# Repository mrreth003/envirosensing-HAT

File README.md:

# Envirosensing HAT PCB Design Group Project (EEE3088F)

## Design Team

- Ethan Morris (MRRETH003)
- Ethan Meknassi (MKNETH002)
- Moutloatsi Setlogelo (STLMOU001)

## Project Overview

Our project involves designing a proximity sensor surveillance device using a HAT (Hardware Attached on Top) powered by either a microcontroller or a battery. The HAT utilizes a PIR motion sensor to detect the presence of a person or animal, triggering a buzzer to sound an alert. Detection logs are stored and can be accessed by the user.

## Hardware Requirements

To operate this device, you will need the following hardware:
- **Power Source**: Either an STM32000 microcontroller or an 18650 battery.
- **USB Cable**: Male USB A to Male Micro USB B Cable for data retrieval.
- **Computer**: For data retrieval and battery charging.

## Hardware Setup

### Microcontroller Power Setup
1. Place the microcontroller under the device using the inner set of connectors.
2. Connect the 5V pin of the microcontroller to pin "J3" on the device. Pin "J3" is the leftmost pin on the third row of connectors when the device is in its default position (buzzer at the top left).

### Battery Power Setup
1. Insert the 18650 battery into the battery holder.
2. Connect the USB to Micro USB cable to the device and your computer for data retrieval or battery charging. The battery should be placed in the position indicated by the red rectangle in the attached picture.

## Basic Operating Instructions

1. Power on the device using the battery.
2. Create movement close to the device (e.g., wave your hand 5-10 cm away from the device). The buzzer should beep, indicating the device is operational.
3. To retrieve the detection log, connect the device to a computer using the USB to Micro USB cable.

## License

The license information for this project can be found in the Git repository.

[Project Repository](https://gitlab.com/mrreth003/envirosensing-hat/-/tree/main/)

Kind Regards,

Ethan Morris, Ethan Meknassi, and Moutloatsi Setlogelo

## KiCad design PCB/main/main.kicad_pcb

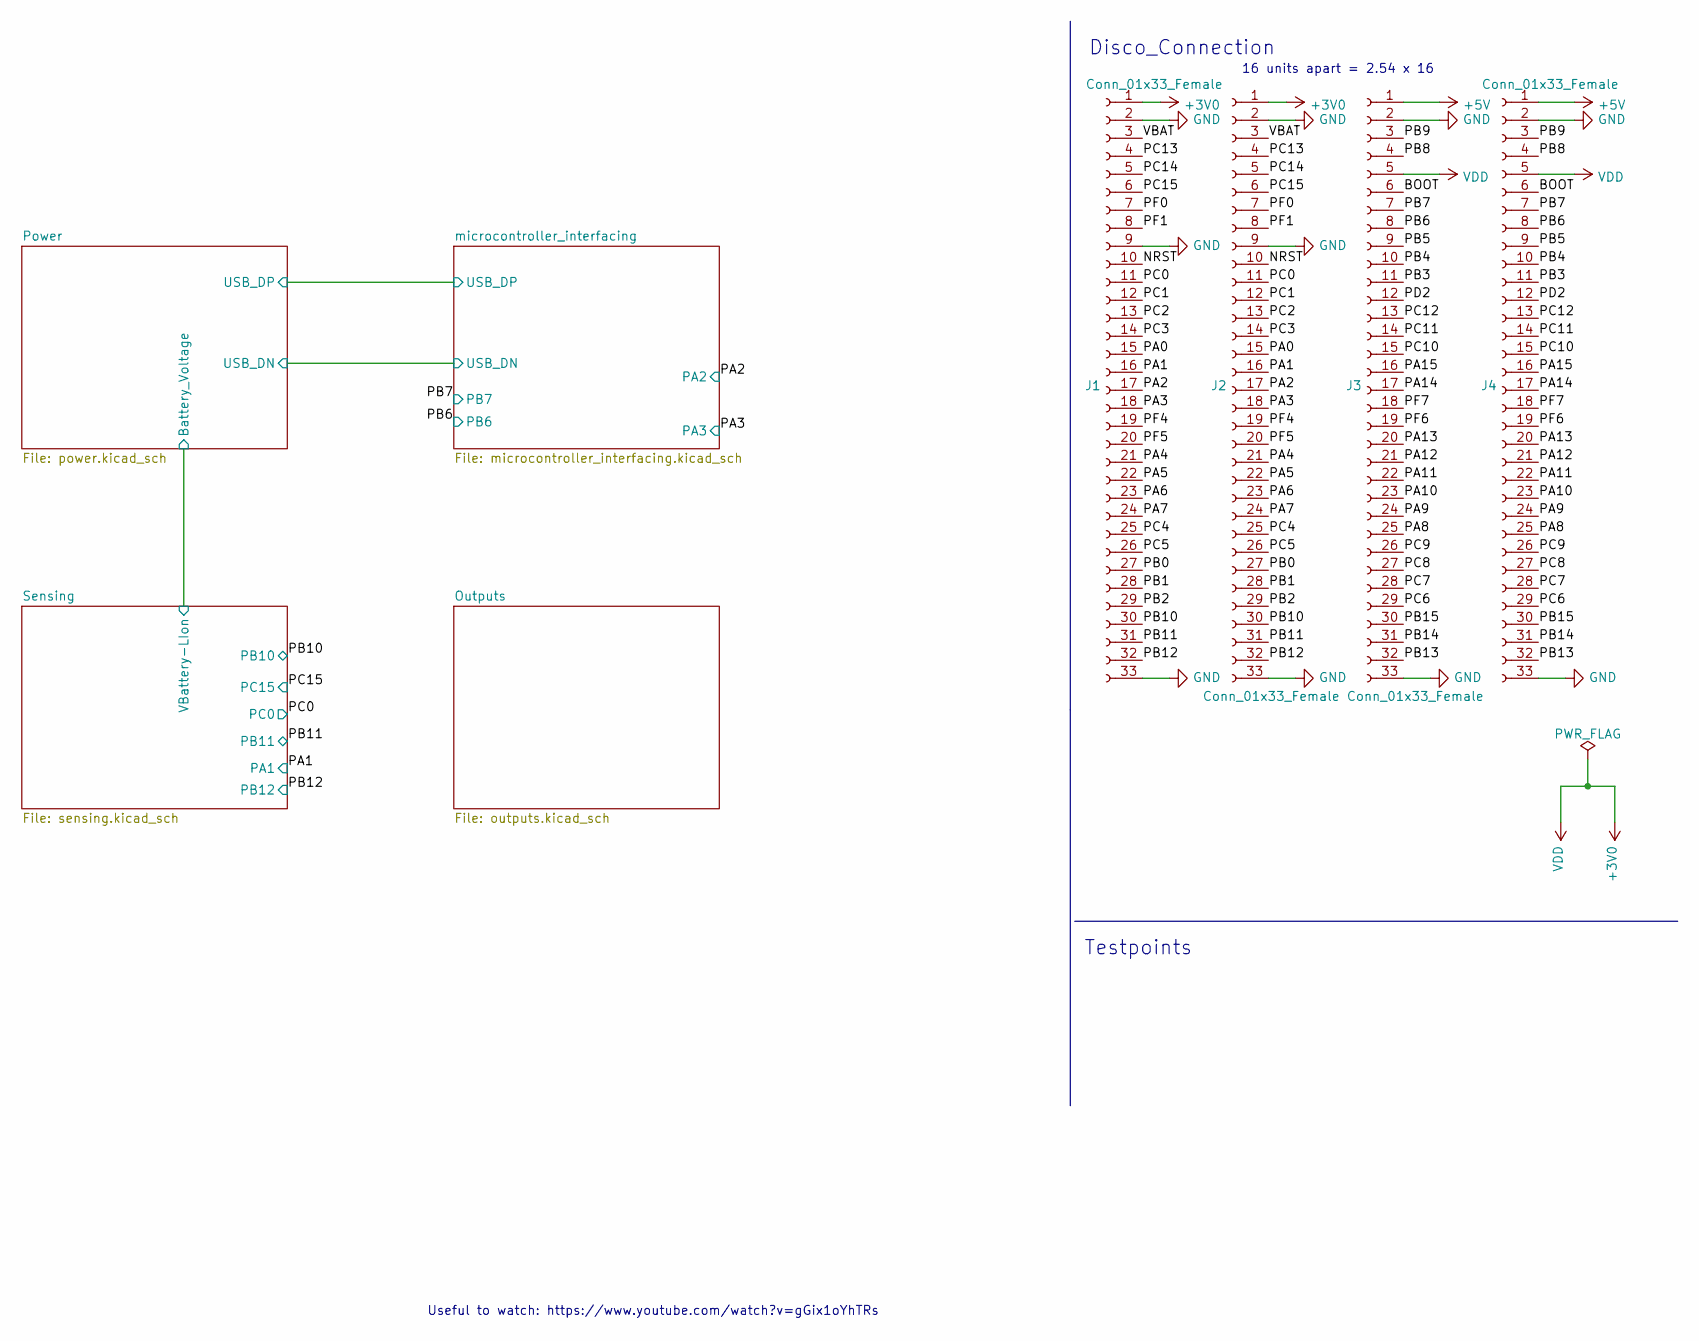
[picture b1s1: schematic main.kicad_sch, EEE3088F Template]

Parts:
J1, J4: Conn_01x33_Female; PinHeader_1x33_P2.54mm_Vertical
J2, J3: Conn_01x33_Female; PinSocket_1x33_P2.54mm_Vertical

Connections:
+3V0: J1.1, J2.1, J3.5, J4.5
+5V: J3.1, J4.1; also elsewhere on the board
/BOOT: J3.6, J4.6
/NRST: J1.10, J2.10
/PA0: J1.15, J2.15
/PA1: J1.16, J2.16; also elsewhere on the board
/PA2: J1.17, J2.17; also elsewhere on the board
/PA3: J1.18, J2.18; also elsewhere on the board
/PA4: J1.21, J2.21
/PA5: J1.22, J2.22
/PA6: J1.23, J2.23
/PA7: J1.24, J2.24
/PA8: J3.25, J4.25
/PA9: J3.24, J4.24
/PA10: J3.23, J4.23
/PA11: J3.22, J4.22
/PA12: J3.21, J4.21
/PA13: J3.20, J4.20
/PA14: J3.17, J4.17
/PA15: J3.16, J4.16
/PB0: J1.27, J2.27
/PB1: J1.28, J2.28
/PB2: J1.29, J2.29
/PB3: J3.11, J4.11
/PB4: J3.10, J4.10
/PB5: J3.9, J4.9
/PB6: J3.8, J4.8; also elsewhere on the board
/PB7: J3.7, J4.7; also elsewhere on the board
/PB8: J3.4, J4.4
/PB9: J3.3, J4.3
/PB10: J1.30, J2.30; also elsewhere on the board
/PB11: J1.31, J2.31; also elsewhere on the board
/PB12: J1.32, J2.32; also elsewhere on the board
/PB13: J3.32, J4.32
/PB14: J3.31, J4.31
/PB15: J3.30, J4.30
/PC0: J1.11, J2.11; also elsewhere on the board
/PC1: J1.12, J2.12
/PC2: J1.13, J2.13
/PC3: J1.14, J2.14
/PC4: J1.25, J2.25
/PC5: J1.26, J2.26
/PC6: J3.29, J4.29
/PC7: J3.28, J4.28
/PC8: J3.27, J4.27
/PC9: J3.26, J4.26
/PC10: J3.15, J4.15
/PC11: J3.14, J4.14
/PC12: J3.13, J4.13
/PC13: J1.4, J2.4
/PC14: J1.5, J2.5
/PC15: J1.6, J2.6; also elsewhere on the board
/PD2: J3.12, J4.12
/PF0: J1.7, J2.7
/PF1: J1.8, J2.8
/PF4: J1.19, J2.19
/PF5: J1.20, J2.20
/PF6: J3.19, J4.19
/PF7: J3.18, J4.18
/VBAT: J1.3, J2.3
GND: J1.2, J1.9, J1.33, J2.2, J2.9, J2.33, J3.2, J3.33, J4.2, J4.33; also elsewhere on the board

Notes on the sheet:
Useful to watch: https://www.youtube.com/watch?v=gGix1oYhTRs
16 units apart = 2.54 x 16
Disco_Connection
Testpoints

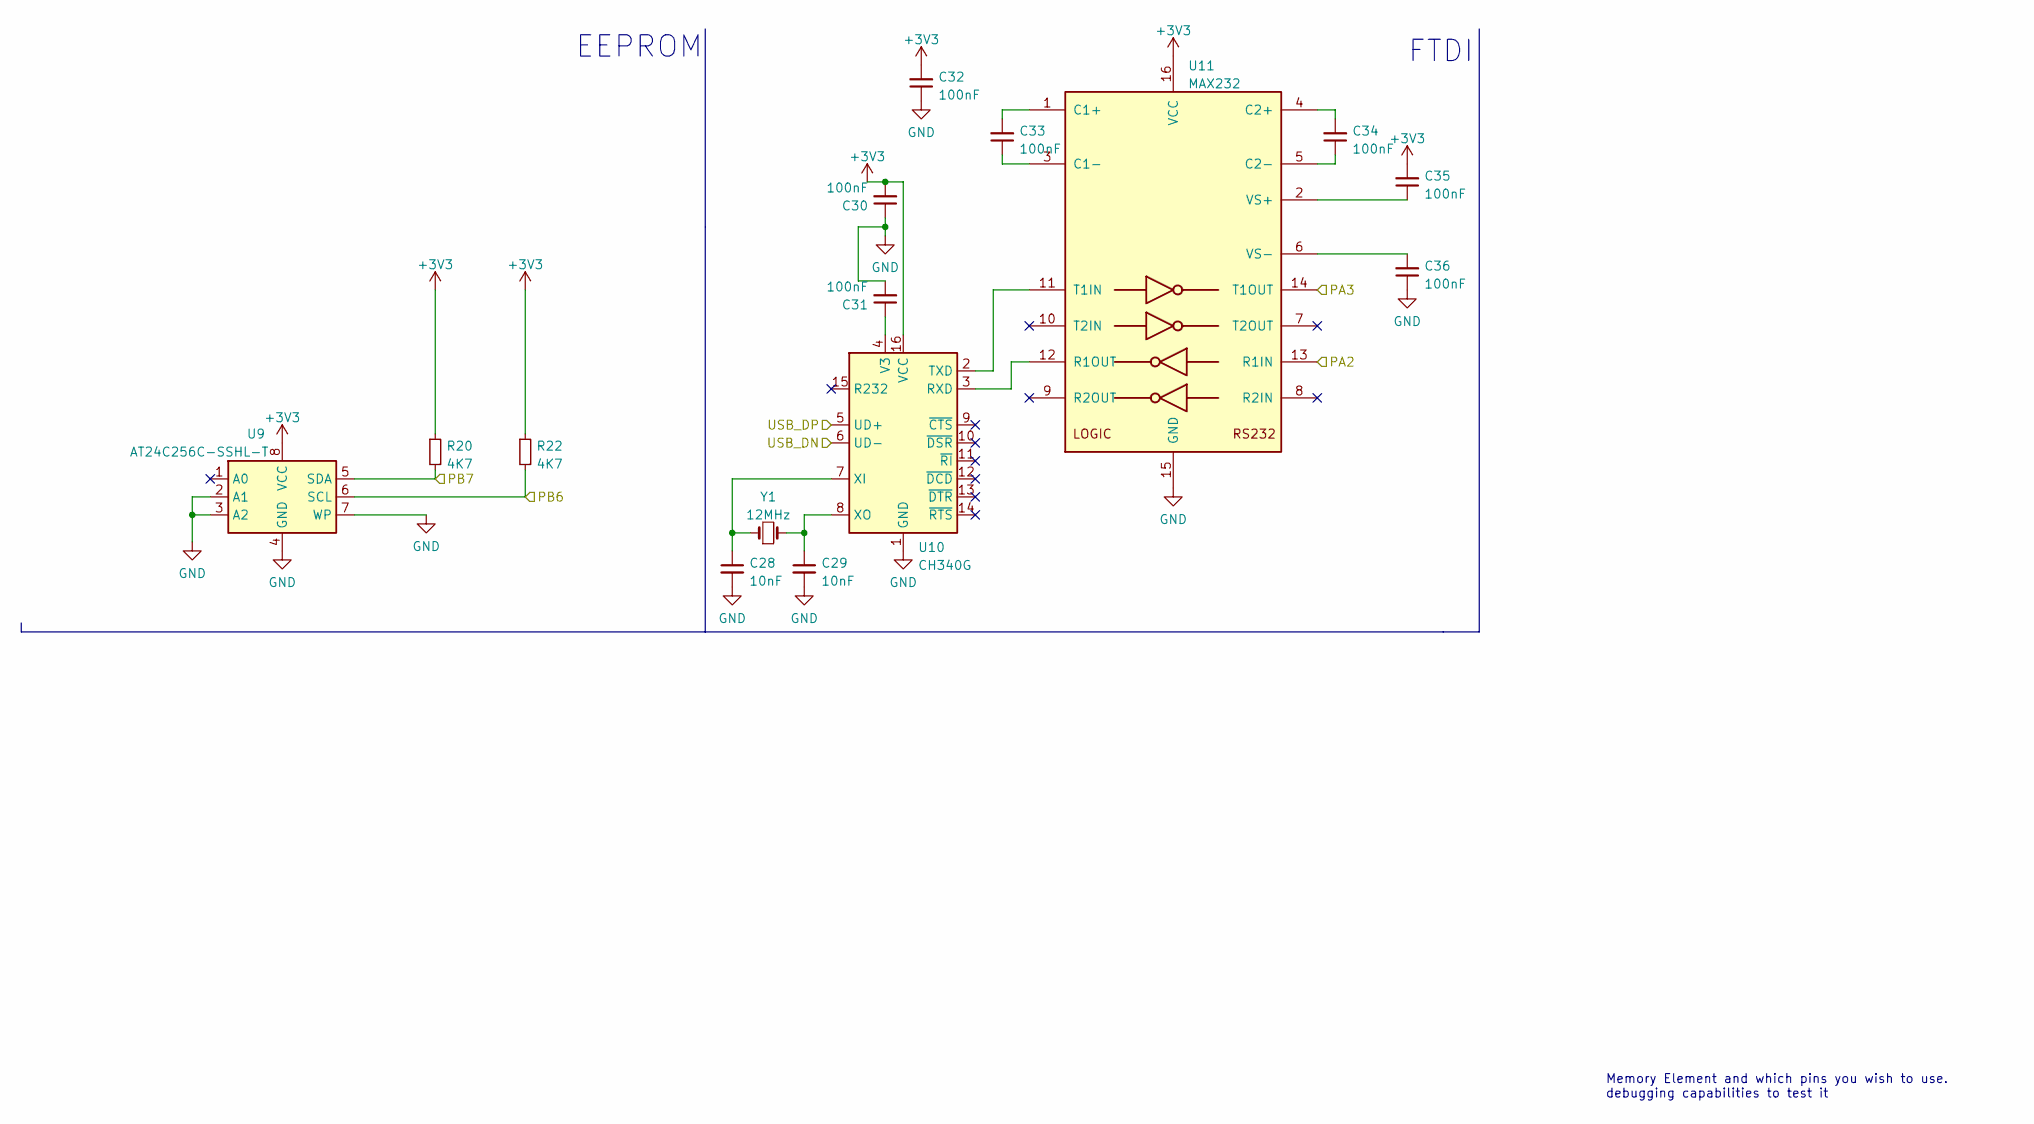
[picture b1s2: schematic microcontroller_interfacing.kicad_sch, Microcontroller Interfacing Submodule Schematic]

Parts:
C28, C29: 10nF; C_0603_1608Metric; LCSC C57112
C30, C31, C32, C33, C34, C35, C36: 100nF; C_0603_1608Metric; LCSC C14663
R20, R22: 4K7; R_0603_1608Metric; LCSC C23162
U9: AT24C256C-SSHL-T; SOIC-8_3.9x4.9mm_P1.27mm; LCSC C6482
U10: CH340G; SOIC-16_3.9x9.9mm_P1.27mm; LCSC C14267
U11: MAX232; SOIC-16_3.9x9.9mm_P1.27mm; LCSC C26860
Y1: 12MHz; Crystal_SMD_3225-4Pin_3.2x2.5mm; LCSC C9002

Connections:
+3V3: C30.2, C32.2, C35.2, R20.1, R22.1, U9.8 (VCC), U10.16 (VCC), U11.16 (VCC); also elsewhere on the board
/PA2: U11.13 (R1IN); also elsewhere on the board
/PA3: U11.14 (T1OUT); also elsewhere on the board
/PB6: R22.2, U9.6 (SCL); also elsewhere on the board
/PB7: R20.2, U9.5 (SDA); also elsewhere on the board
/Power/USB_DN: U10.6 (UD-); also elsewhere on the board
/Power/USB_DP: U10.5 (UD+); also elsewhere on the board
GND: C28.2, C29.2, C30.1, C31.2, C32.1, C36.1, U9.2 (A1), U9.3 (A2), U9.4 (GND), U9.7 (WP), U10.1 (GND), U11.15 (GND); also elsewhere on the board
unnamed: C28.1, U10.7 (XI), Y1.1
unnamed: C29.1, U10.8 (XO), Y1.2
unnamed: C31.1, U10.4 (V3)
unnamed: C33.1, U11.3 (C1-)
unnamed: C33.2, U11.1 (C1+)
unnamed: C34.1, U11.5 (C2-)
unnamed: C34.2, U11.4 (C2+)
unnamed: C35.1, U11.2 (VS+)
unnamed: C36.2, U11.6 (VS-)
unnamed: U10.2 (TXD), U11.11 (T1IN)
unnamed: U10.3 (RXD), U11.12 (R1OUT)

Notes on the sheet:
FTDI
EEPROM
Memory Element and which pins you wish to use. debugging capabilities to test it

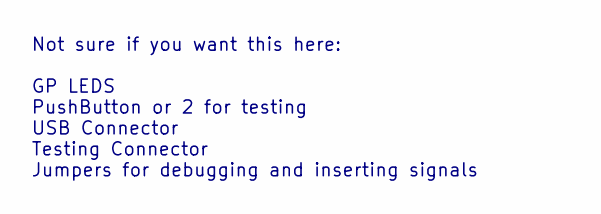
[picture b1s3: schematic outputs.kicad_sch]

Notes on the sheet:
Not sure if you want this here: GP LEDS PushButton or 2 for testing USB Connector Testing Connector Jumpers for debugging and inserting signals

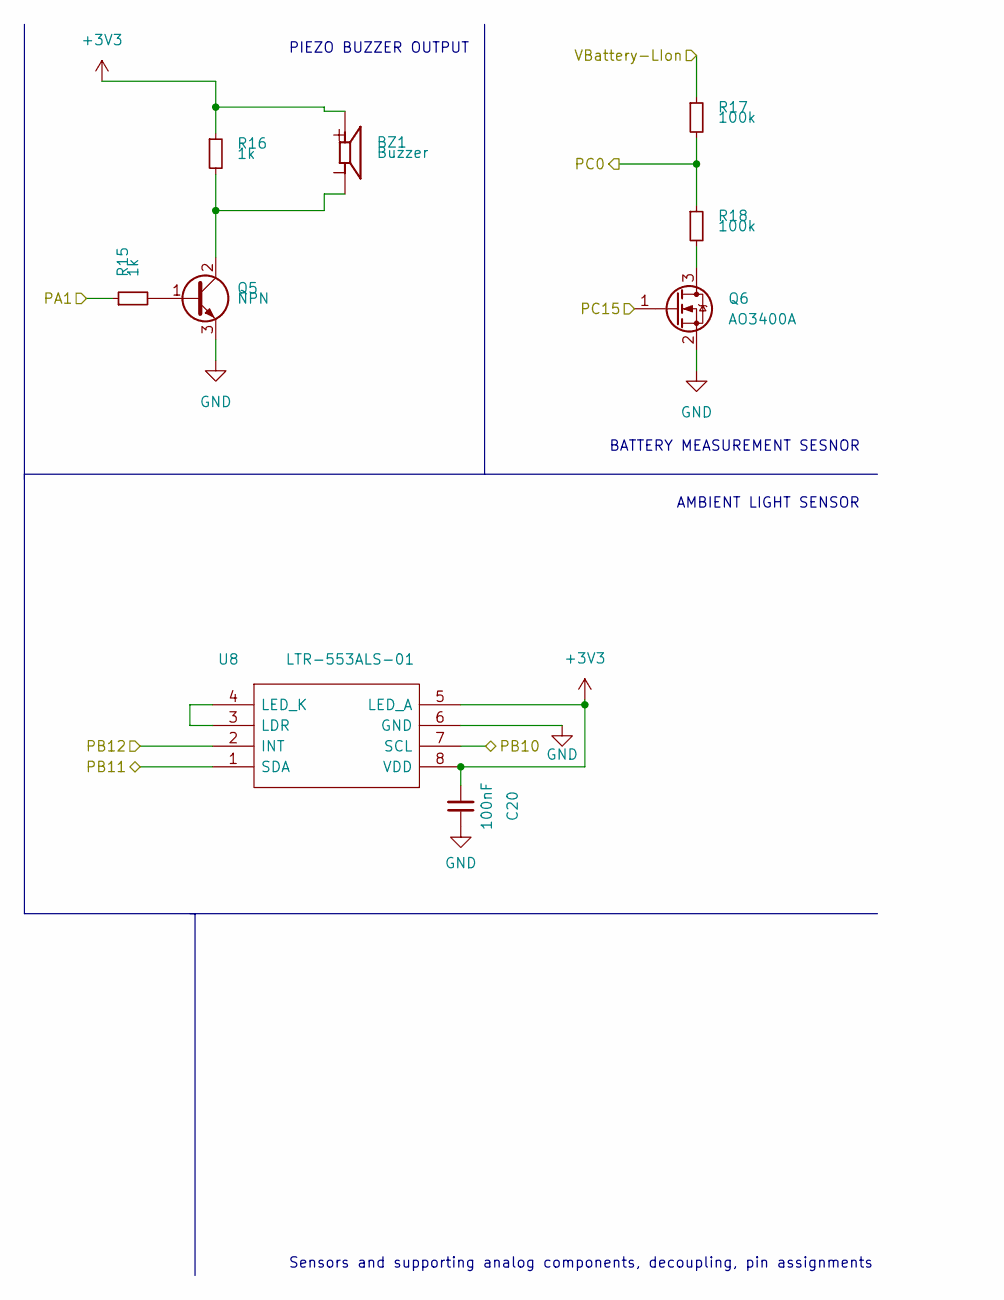
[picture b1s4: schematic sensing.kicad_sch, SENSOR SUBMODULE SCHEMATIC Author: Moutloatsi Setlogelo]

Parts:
BZ1: Buzzer; SPKR_PKM13EPYH4002-B0; LCSC C128650
C20: 100nF; C_0603_1608Metric; LCSC C14663
Q5: NPN; SOT-23; LCSC C20526
Q6: AO3400A; SOT-23; LCSC C20917
R15, R16: 1k; R_0805_2012Metric; LCSC C17513
R17, R18: 100k; R_1206_3216Metric; LCSC C17900
U8: LTR-553ALS-01; LTR553ALS01; LCSC C492375

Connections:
+3V3: BZ1.P, C20.2, R16.1, U8.5 (LED_A), U8.8 (VDD); also elsewhere on the board
/PA1: R15.1; also elsewhere on the board
/PB10: U8.7 (SCL); also elsewhere on the board
/PB11: U8.1 (SDA); also elsewhere on the board
/PB12: U8.2 (INT); also elsewhere on the board
/PC0: R17.2, R18.1; also elsewhere on the board
/PC15: Q6.1 (G); also elsewhere on the board
/Power/Battery_Voltage: R17.1; also elsewhere on the board
GND: C20.1, Q5.3 (E), Q6.2 (S), U8.6 (GND); also elsewhere on the board
unnamed: BZ1.N, Q5.2 (C), R16.2
unnamed: Q5.1 (B), R15.2
unnamed: Q6.3 (D), R18.2
unnamed: U8.3 (LDR), U8.4 (LED_K)

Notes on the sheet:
AMBIENT LIGHT SENSOR
Sensors and supporting analog components, decoupling, pin assignments
PIEZO BUZZER OUTPUT
BATTERY MEASUREMENT SESNOR

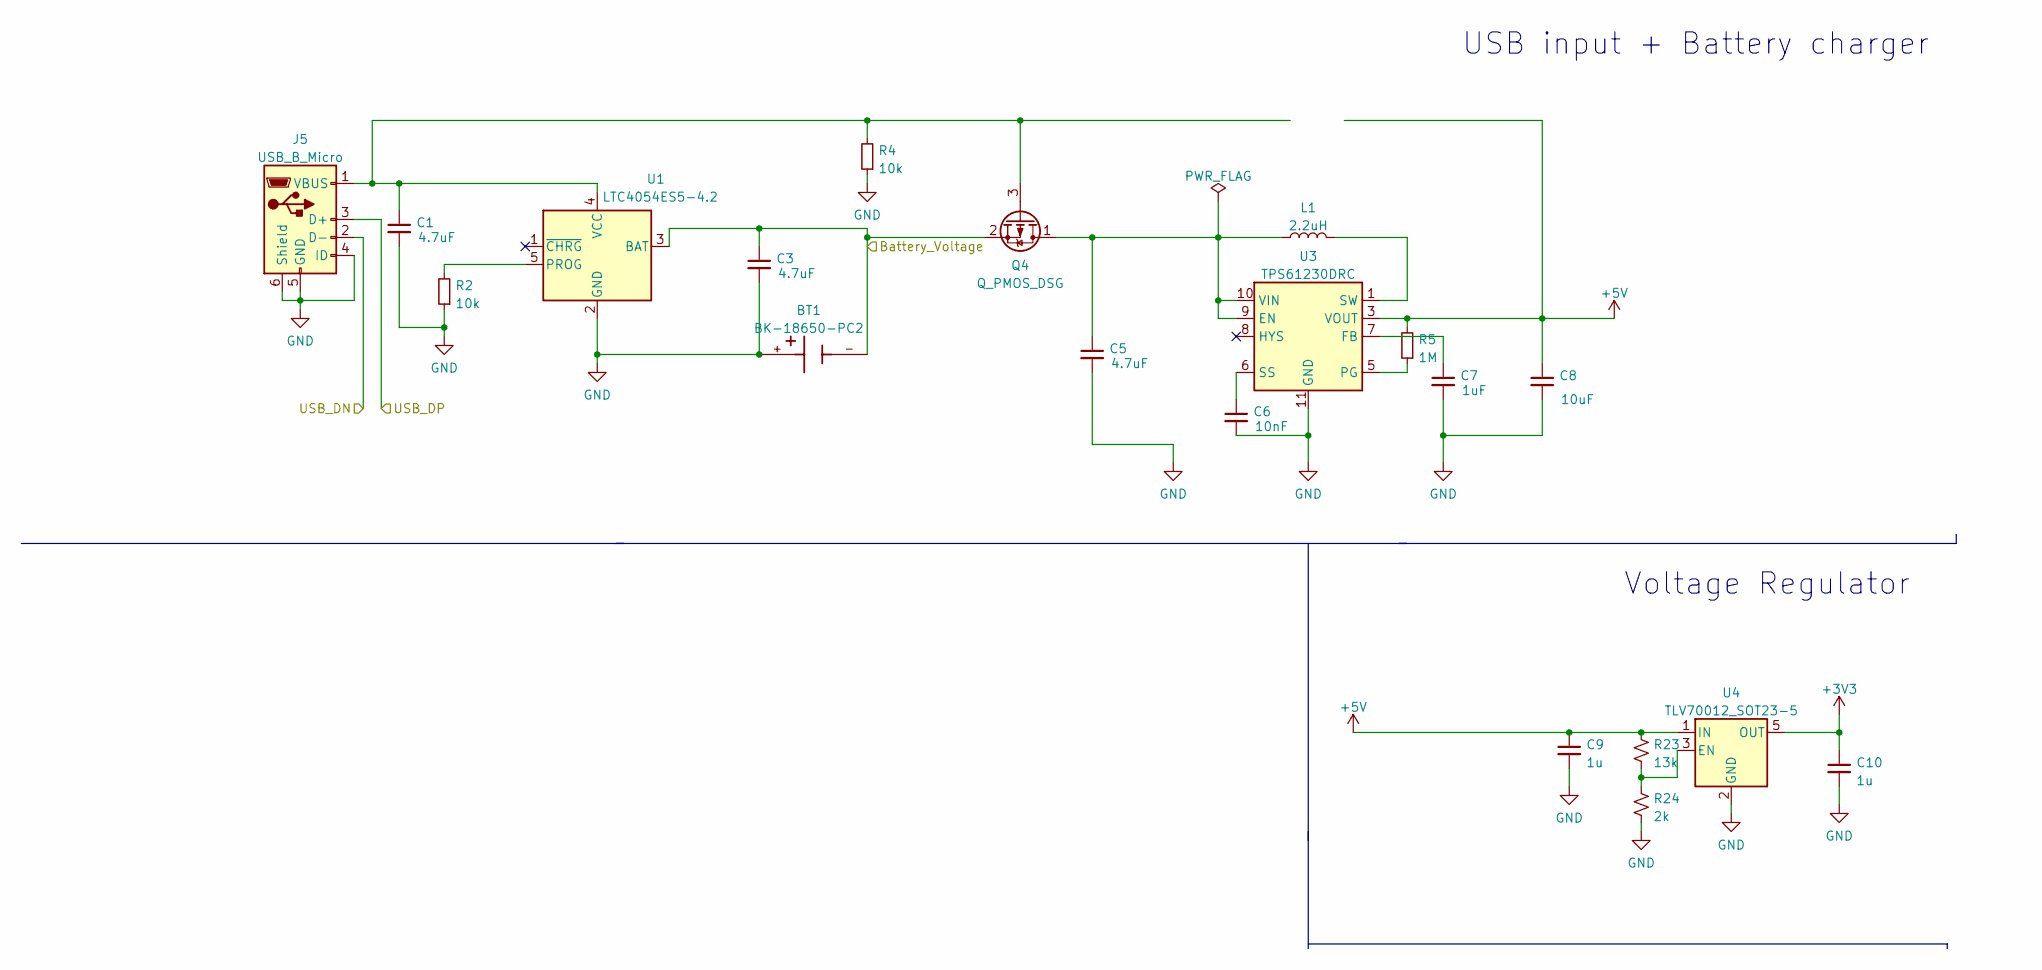
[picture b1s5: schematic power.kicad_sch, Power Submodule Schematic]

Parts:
BT1: BK-18650-PC2; BAT_BK-18650-PC2; PARTREV F
C1, C3, C5: 4.7uF; C_1206_3216Metric; LCSC C29823
C6: 10nF; C_0603_1608Metric; LCSC C57112
C7: 1uF; C_0603_1608Metric; LCSC C15849
C8: 10uF; C_1206_3216Metric; LCSC C13585
C9, C10: 1u; C_0603_1608Metric; LCSC C15849
J5: USB_B_Micro; USB_Micro-B_Molex-105133-0031; LCSC C132563
L1: 2.2uH; L_0805_2012Metric; LCSC C1043
Q4: Q_PMOS_DSG; SOT-23; LCSC C8492
R2, R4: 10k; R_0603_1608Metric; LCSC C25804
R5: 1M; R_0603_1608Metric; LCSC C22935
R23: 13k; R_0603_1608Metric; LCSC C22797
R24: 2k; R_0603_1608Metric; LCSC C22975
U1: LTC4054ES5-4.2; TSOT-23-5; LCSC C32574
U3: TPS61230DRC; Texas_S-PVSON-N10_ThermalVias; LCSC C139626
U4: TLV70012_SOT23-5; SOT-23-5; LCSC C134139

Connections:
+3V3: C10.1, U4.5 (OUT); also elsewhere on the board
+5V: C8.1, C9.1, R5.2, R23.1, U3.3 (VOUT), U3.4 (VOUT), U4.1 (IN); also elsewhere on the board
/Power/Battery_Voltage: BT1.-, C3.1, Q4.2 (S), U1.3 (BAT); also elsewhere on the board
/Power/USB_DN: J5.2 (D-); also elsewhere on the board
/Power/USB_DP: J5.3 (D+); also elsewhere on the board
GND: BT1.+, C1.2, C3.2, C5.2, C6.2, C7.2, C8.2, C9.2, C10.2, J5.4 (ID), J5.5 (GND), J5.6 (Shield), R2.1, R4.1, R24.2, U1.2 (GND), U3.11 (GND), U4.2 (GND); also elsewhere on the board
unnamed 66: C1.1, J5.1 (VBUS), Q4.3 (G), R4.2, U1.4 (VCC); also elsewhere on the board
unnamed: C5.1, L1.1, Q4.1 (D), U3.9 (EN), U3.10 (VIN)
unnamed: C6.1, U3.6 (SS)
unnamed: C7.1, U3.7 (FB)
unnamed: L1.2, U3.1 (SW), U3.2 (SW)
unnamed: R2.2, U1.5 (PROG)
unnamed: R5.1, U3.5 (PG)
unnamed: R23.2, R24.1, U4.3 (EN)

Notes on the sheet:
USB input + Battery charger
Voltage Regulator

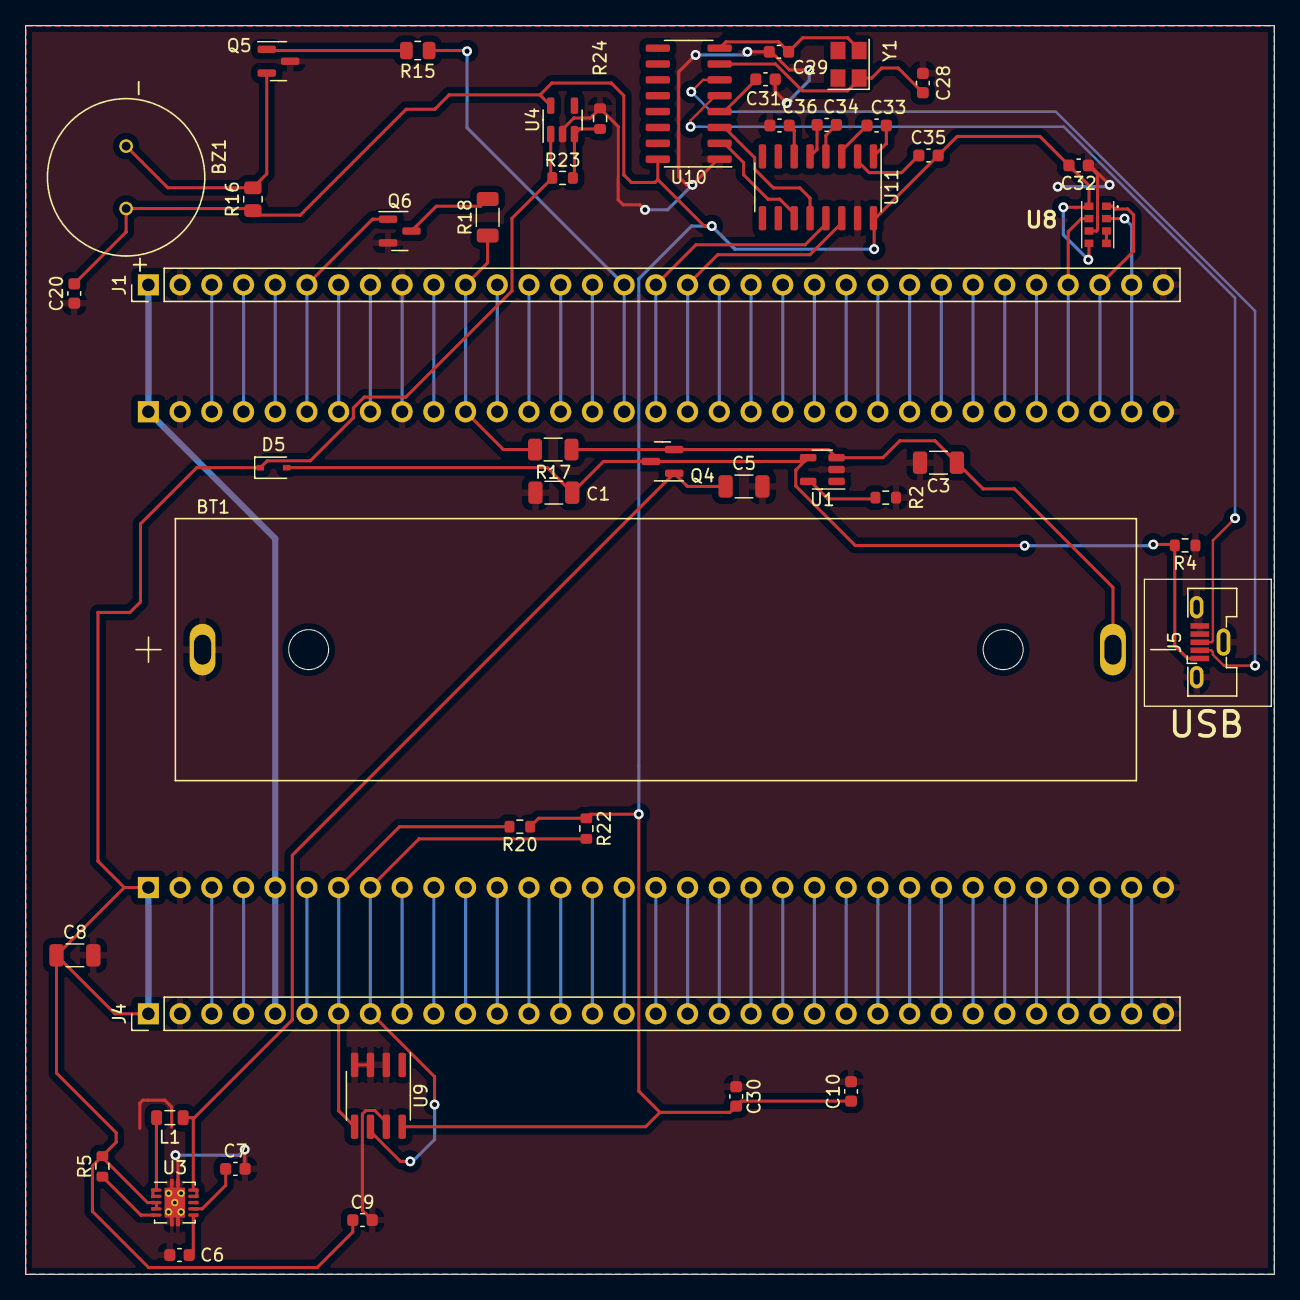
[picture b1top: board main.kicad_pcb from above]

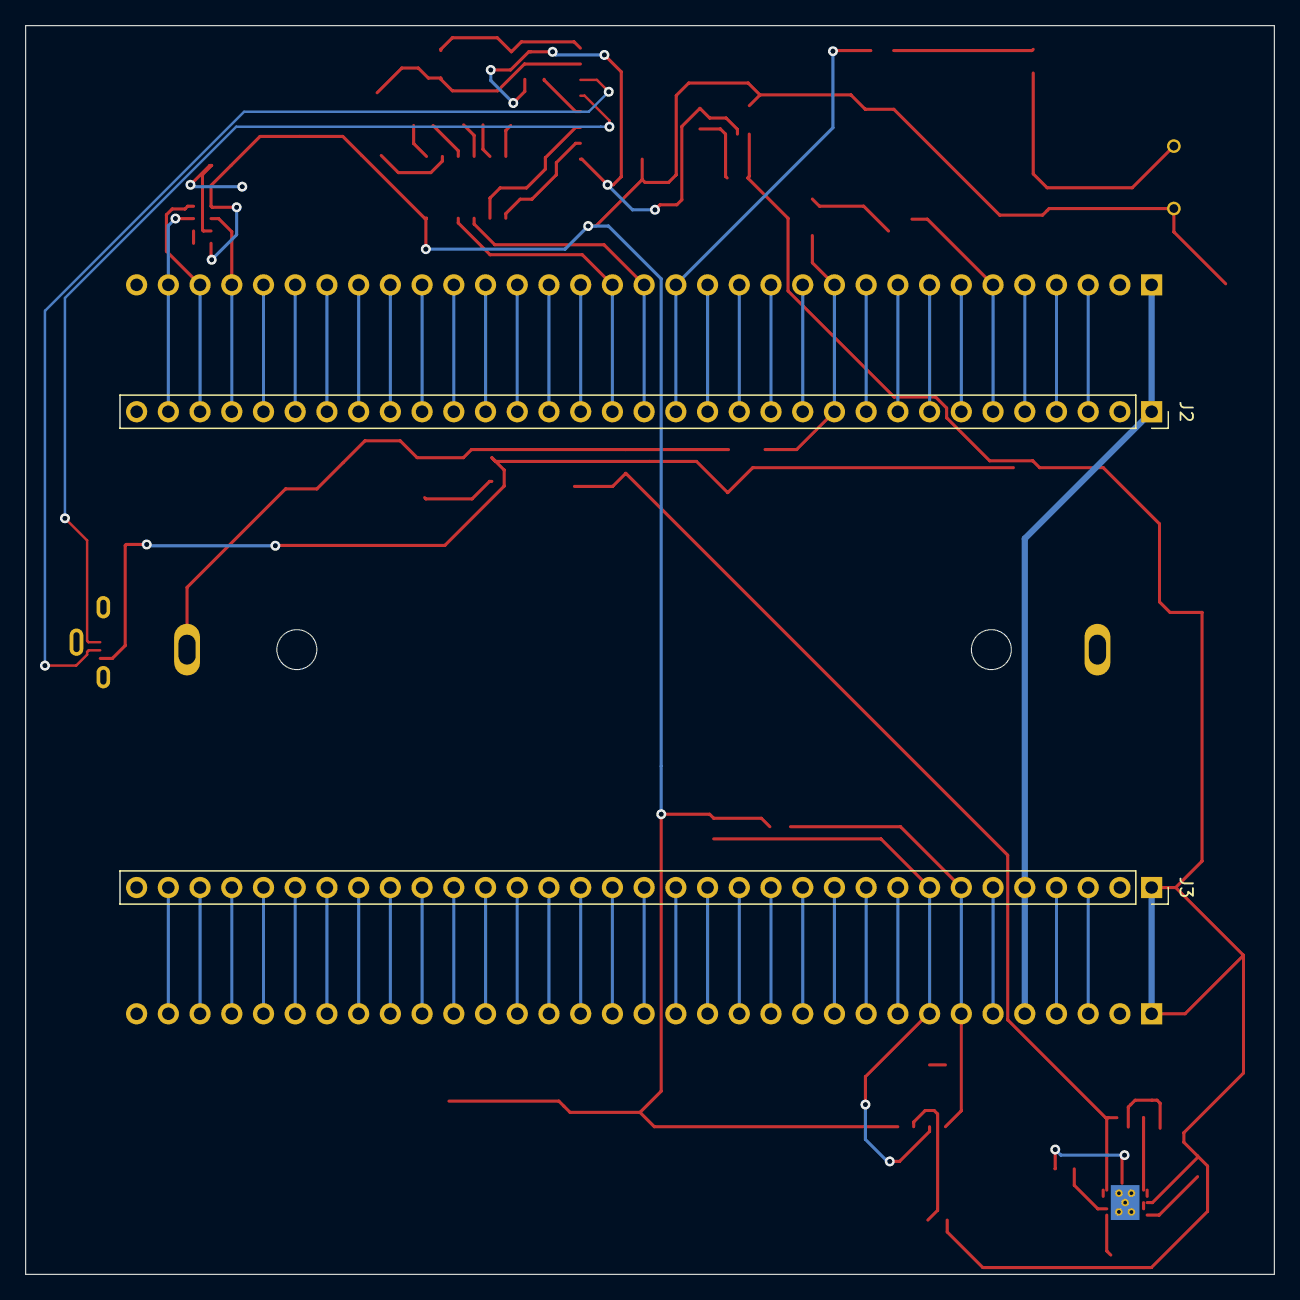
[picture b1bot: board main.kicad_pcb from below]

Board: 2 copper layers, 100.0 x 100.0 mm, 49 parts (2 on the bottom side), 88 nets.

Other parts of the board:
D5: D_Schottky; D_SOD-323

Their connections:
+5V: D5.1 (K); also elsewhere on the board
unnamed 66: D5.2 (A); also elsewhere on the board

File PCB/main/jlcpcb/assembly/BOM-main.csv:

Comment,Designator,Footprint,LCSC
2.2uH,L1,L_0805_2012Metric,C1043
Buzzer,BZ1,SPKR_PKM13EPYH4002-B0,C128650
USB_B_Micro,J5,USB_Micro-B_Molex-105133-0031,C132563
TLV70012_SOT23-5,U4,SOT-23-5,C134139
10uF,C8,C_1206_3216Metric,C13585
TPS61230DRC,U3,Texas_S-PVSON-N10_ThermalVias,C139626
CH340G,U10,SOIC-16_3.9x9.9mm_P1.27mm,C14267
100nF,"C20,C30,C31,C32,C33,C34,C35,C36",C_0603_1608Metric,C14663
1u,"C10,C7,C9",C_0603_1608Metric,C15849
1k,"R15,R16",R_0805_2012Metric,C17513
100k,"R17,R18",R_1206_3216Metric,C17900
NPN,Q5,SOT-23,C20526
AO3400A,Q6,SOT-23,C20917
13k,R23,R_0603_1608Metric,C22797
1M,R5,R_0603_1608Metric,C22935
2k,R24,R_0603_1608Metric,C22975
4K7,"R20,R22",R_0603_1608Metric,C23162
10k,"R2,R4",R_0603_1608Metric,C25804
MAX232,U11,SOIC-16_3.9x9.9mm_P1.27mm,C26860
4.7uF,"C1,C3,C5",C_1206_3216Metric,C29823
LTC4054ES5-4.2,U1,TSOT-23-5,C32574
LTR-553ALS-01,U8,LTR553ALS01,C492375
10nF,"C28,C29,C6",C_0603_1608Metric,C57112
AT24C256C-SSHL-T,U9,SOIC-8_3.9x4.9mm_P1.27mm,C6482
Q_PMOS_DSG,Q4,SOT-23,C8492
D_Schottky,D5,D_SOD-323,C8598
12MHz,Y1,Crystal_SMD_3225-4Pin_3.2x2.5mm,C9002
Conn_01x33_Female,J1,PinHeader_1x33_P2.54mm_Vertical,
BK-18650-PC2,BT1,BAT_BK-18650-PC2,
Conn_01x33_Female,J4,PinHeader_1x33_P2.54mm_Vertical,
Conn_01x33_Female,J2,PinSocket_1x33_P2.54mm_Vertical,
Conn_01x33_Female,J3,PinSocket_1x33_P2.54mm_Vertical,

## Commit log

2024-05-29 Final version published
